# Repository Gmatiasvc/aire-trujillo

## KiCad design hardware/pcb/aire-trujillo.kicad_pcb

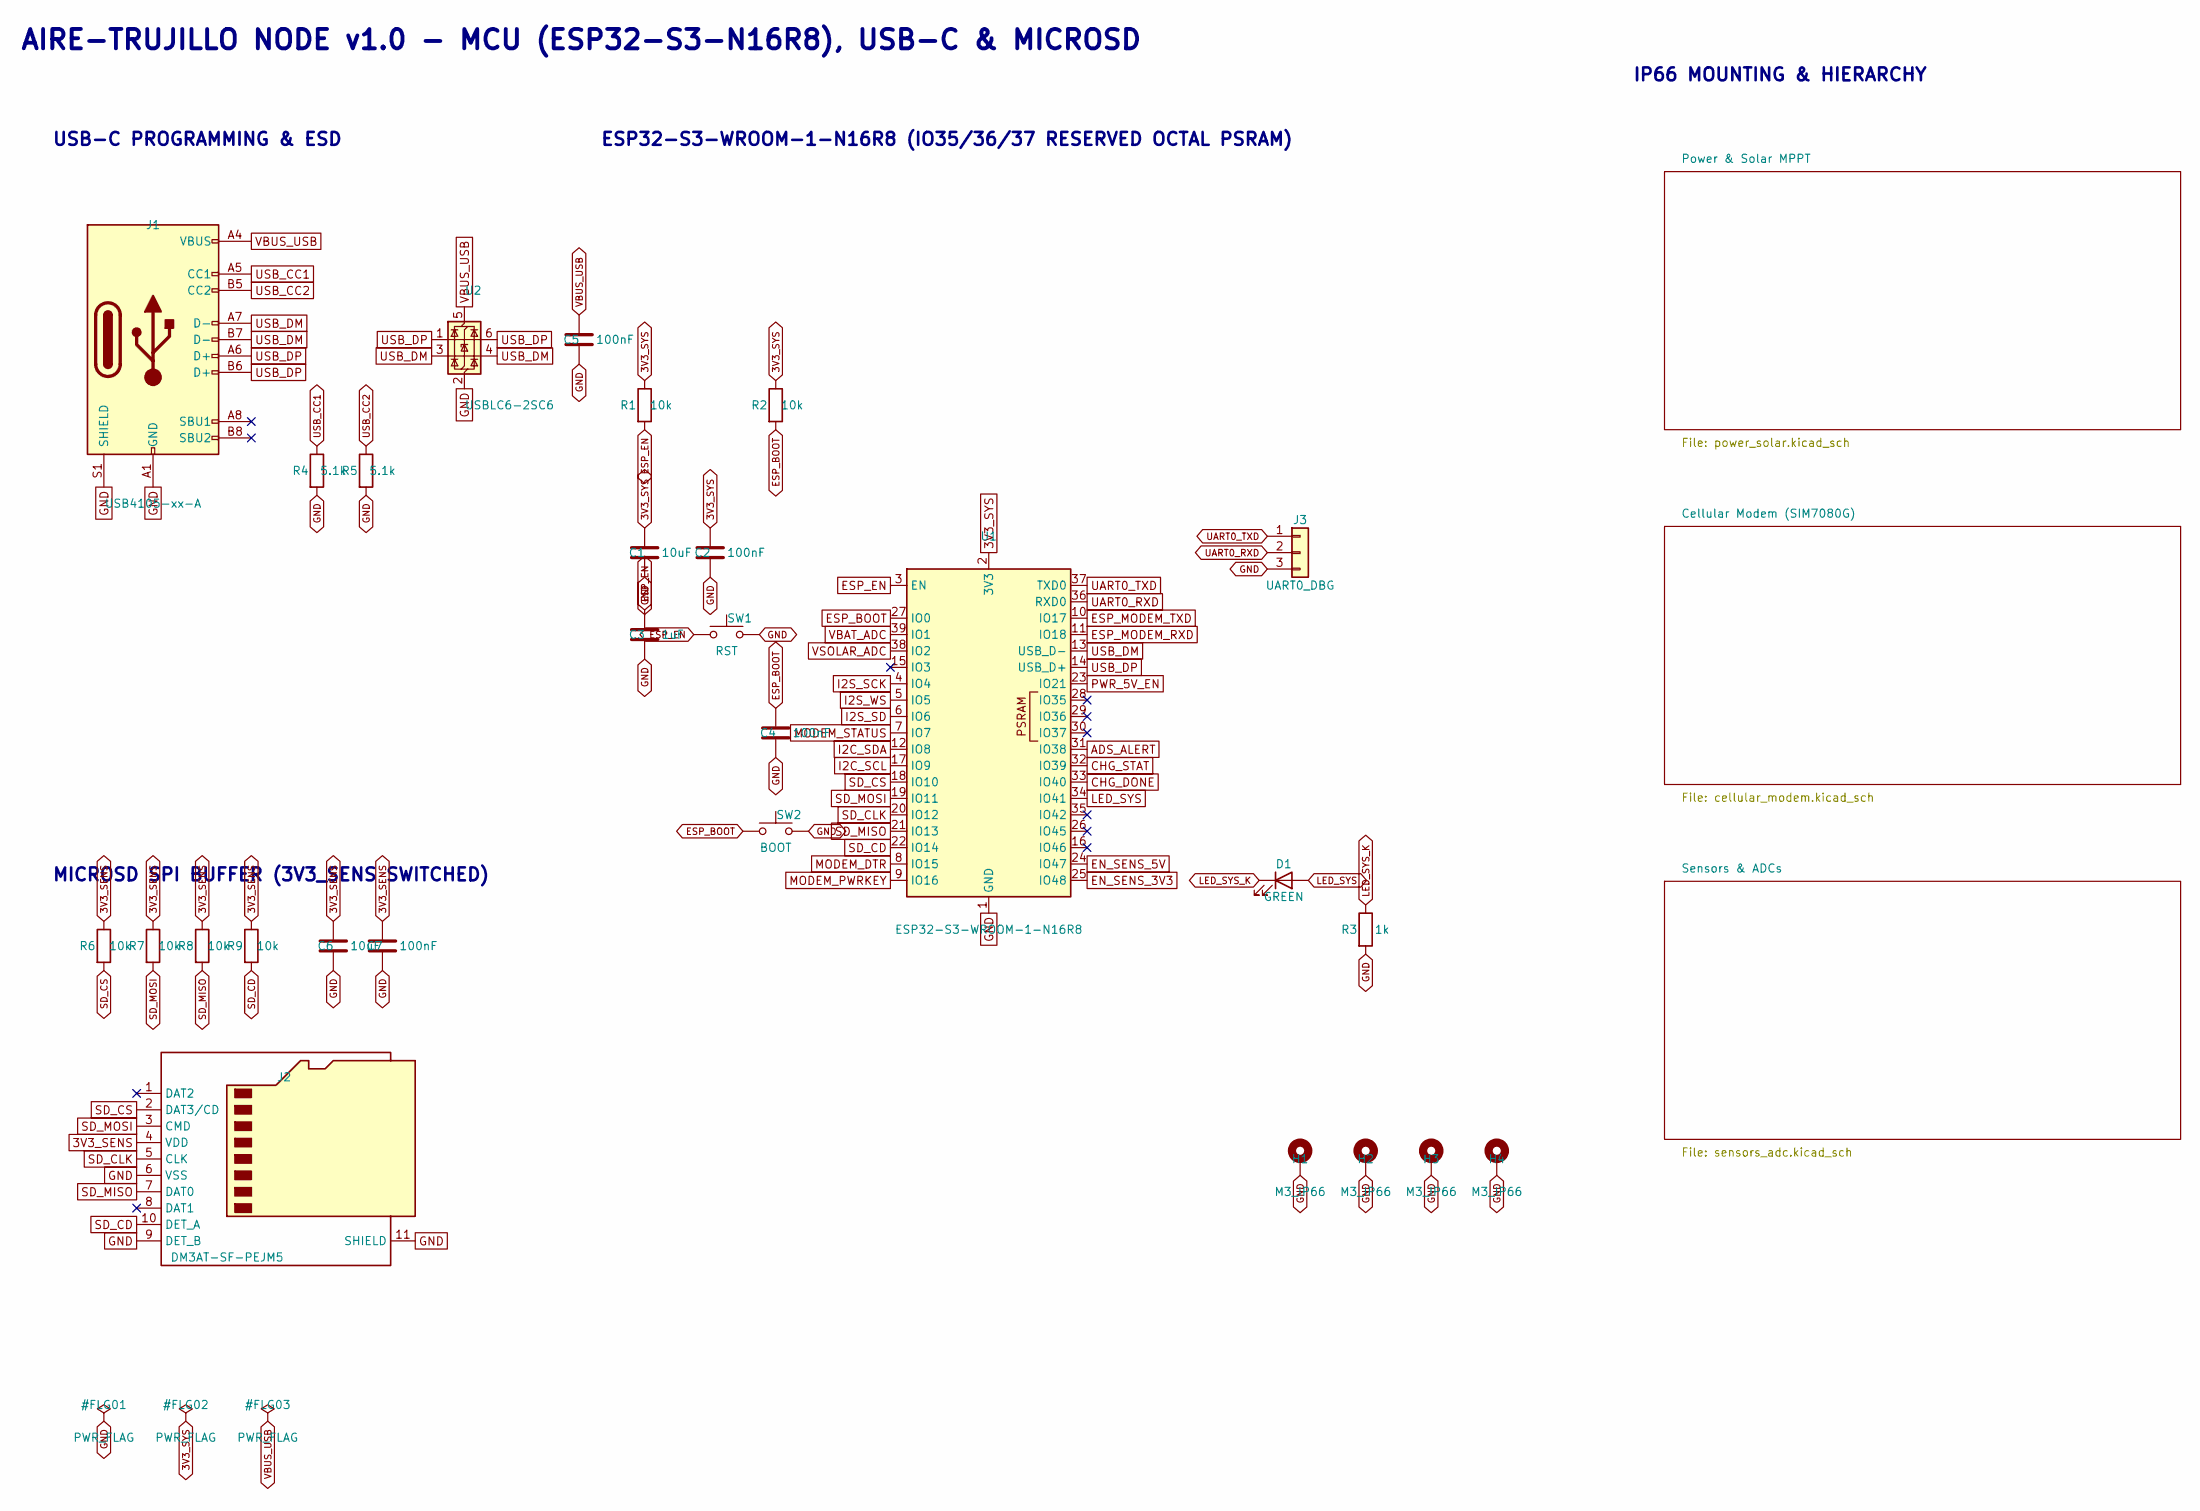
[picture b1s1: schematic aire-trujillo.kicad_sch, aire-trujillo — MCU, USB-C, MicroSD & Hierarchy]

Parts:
C1, C6: 10uF; C_0805_2012Metric
C2, C4, C5, C7: 100nF; C_0603_1608Metric
C3: 1uF; C_0603_1608Metric
D1: GREEN; LED_0603_1608Metric
H1, H2, H3, H4: M3_IP66; MountingHole_3.2mm_M3_ISO14580_Pad_TopBottom
J1: USB4105-xx-A; USB_C_Receptacle_GCT_USB4105-xx-A_16P_TopMnt_Horizontal
J2: DM3AT-SF-PEJM5; microSD_HC_Hirose_DM3AT-SF-PEJM5
J3: UART0_DBG; PinHeader_1x03_P2.54mm_Vertical
R1, R2, R6, R7, R8, R9: 10k; R_0603_1608Metric
R3: 1k; R_0603_1608Metric
R4, R5: 5.1k; R_0603_1608Metric
SW1: RST; SW_SPST_B3U-1000P
SW2: BOOT; SW_SPST_B3U-1000P
U1: ESP32-S3-WROOM-1-N16R8; ESP32-S3-WROOM-1
U2: USBLC6-2SC6; SOT-23-6

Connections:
3V3_SENS: C6.1, C7.1, J2.4 (VDD), R6.1, R7.1, R8.1, R9.1; also elsewhere on the board
3V3_SYS: C1.1, C2.1, R1.1, R2.1, U1.2 (3V3); also elsewhere on the board
ADS_ALERT: U1.31 (IO38); also elsewhere on the board
CHG_DONE: U1.33 (IO40); also elsewhere on the board
CHG_STAT: U1.32 (IO39); also elsewhere on the board
EN_SENS_3V3: U1.25 (IO48); also elsewhere on the board
EN_SENS_5V: U1.24 (IO47); also elsewhere on the board
ESP_BOOT: C4.1, R2.2, SW2.1, U1.27 (IO0)
ESP_EN: C3.1, R1.2, SW1.1, U1.3 (EN)
ESP_MODEM_RXD: U1.11 (IO18); also elsewhere on the board
ESP_MODEM_TXD: U1.10 (IO17); also elsewhere on the board
GND: C1.2, C2.2, C3.2, C4.2, C5.2, C6.2, C7.2, H1.1, H2.1, H3.1, H4.1, J1.A1 (GND), J1.A12 (GND), J1.B1 (GND), J1.B12 (GND), J1.S1 (SHIELD), J2.6 (VSS), J2.9 (DET_B), J2.11 (SHIELD), J3.3, R3.2, R4.2, R5.2, SW1.2, SW2.2, U1.1 (GND), U1.40 (GND), U1.41 (GND), U2.2 (GND); also elsewhere on the board
I2C_SCL: U1.17 (IO9); also elsewhere on the board
I2C_SDA: U1.12 (IO8); also elsewhere on the board
I2S_SCK: U1.4 (IO4); also elsewhere on the board
I2S_SD: U1.6 (IO6); also elsewhere on the board
I2S_WS: U1.5 (IO5); also elsewhere on the board
LED_SYS: D1.2 (A), U1.34 (IO41)
LED_SYS_K: D1.1 (K), R3.1
MODEM_DTR: U1.8 (IO15); also elsewhere on the board
MODEM_PWRKEY: U1.9 (IO16); also elsewhere on the board
MODEM_STATUS: U1.7 (IO7); also elsewhere on the board
PWR_5V_EN: U1.23 (IO21); also elsewhere on the board
SD_CD: J2.10 (DET_A), R9.2, U1.22 (IO14)
SD_CLK: J2.5 (CLK), U1.20 (IO12)
SD_CS: J2.2 (DAT3/CD), R6.2, U1.18 (IO10)
SD_MISO: J2.7 (DAT0), R8.2, U1.21 (IO13)
SD_MOSI: J2.3 (CMD), R7.2, U1.19 (IO11)
UART0_RXD: J3.2, U1.36 (RXD0)
UART0_TXD: J3.1, U1.37 (TXD0)
USB_CC1: J1.A5 (CC1), R4.1
USB_CC2: J1.B5 (CC2), R5.1
USB_DM: J1.A7 (D-), J1.B7 (D-), U1.13 (USB_D-), U2.3 (I/O2), U2.4 (I/O2)
USB_DP: J1.A6 (D+), J1.B6 (D+), U1.14 (USB_D+), U2.1 (I/O1), U2.6 (I/O1)
VBAT_ADC: U1.39 (IO1); also elsewhere on the board
VBUS_USB: C5.1, J1.A4 (VBUS), J1.A9 (VBUS), J1.B4 (VBUS), J1.B9 (VBUS), U2.5 (VBUS); also elsewhere on the board
VSOLAR_ADC: U1.38 (IO2); also elsewhere on the board

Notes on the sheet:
AIRE-TRUJILLO NODE v1.0 - MCU (ESP32-S3-N16R8), USB-C & MICROSD
USB-C PROGRAMMING & ESD
ESP32-S3-WROOM-1-N16R8 (IO35/36/37 RESERVED OCTAL PSRAM)
MICROSD SPI BUFFER (3V3_SENS SWITCHED)
IP66 MOUNTING & HIERARCHY

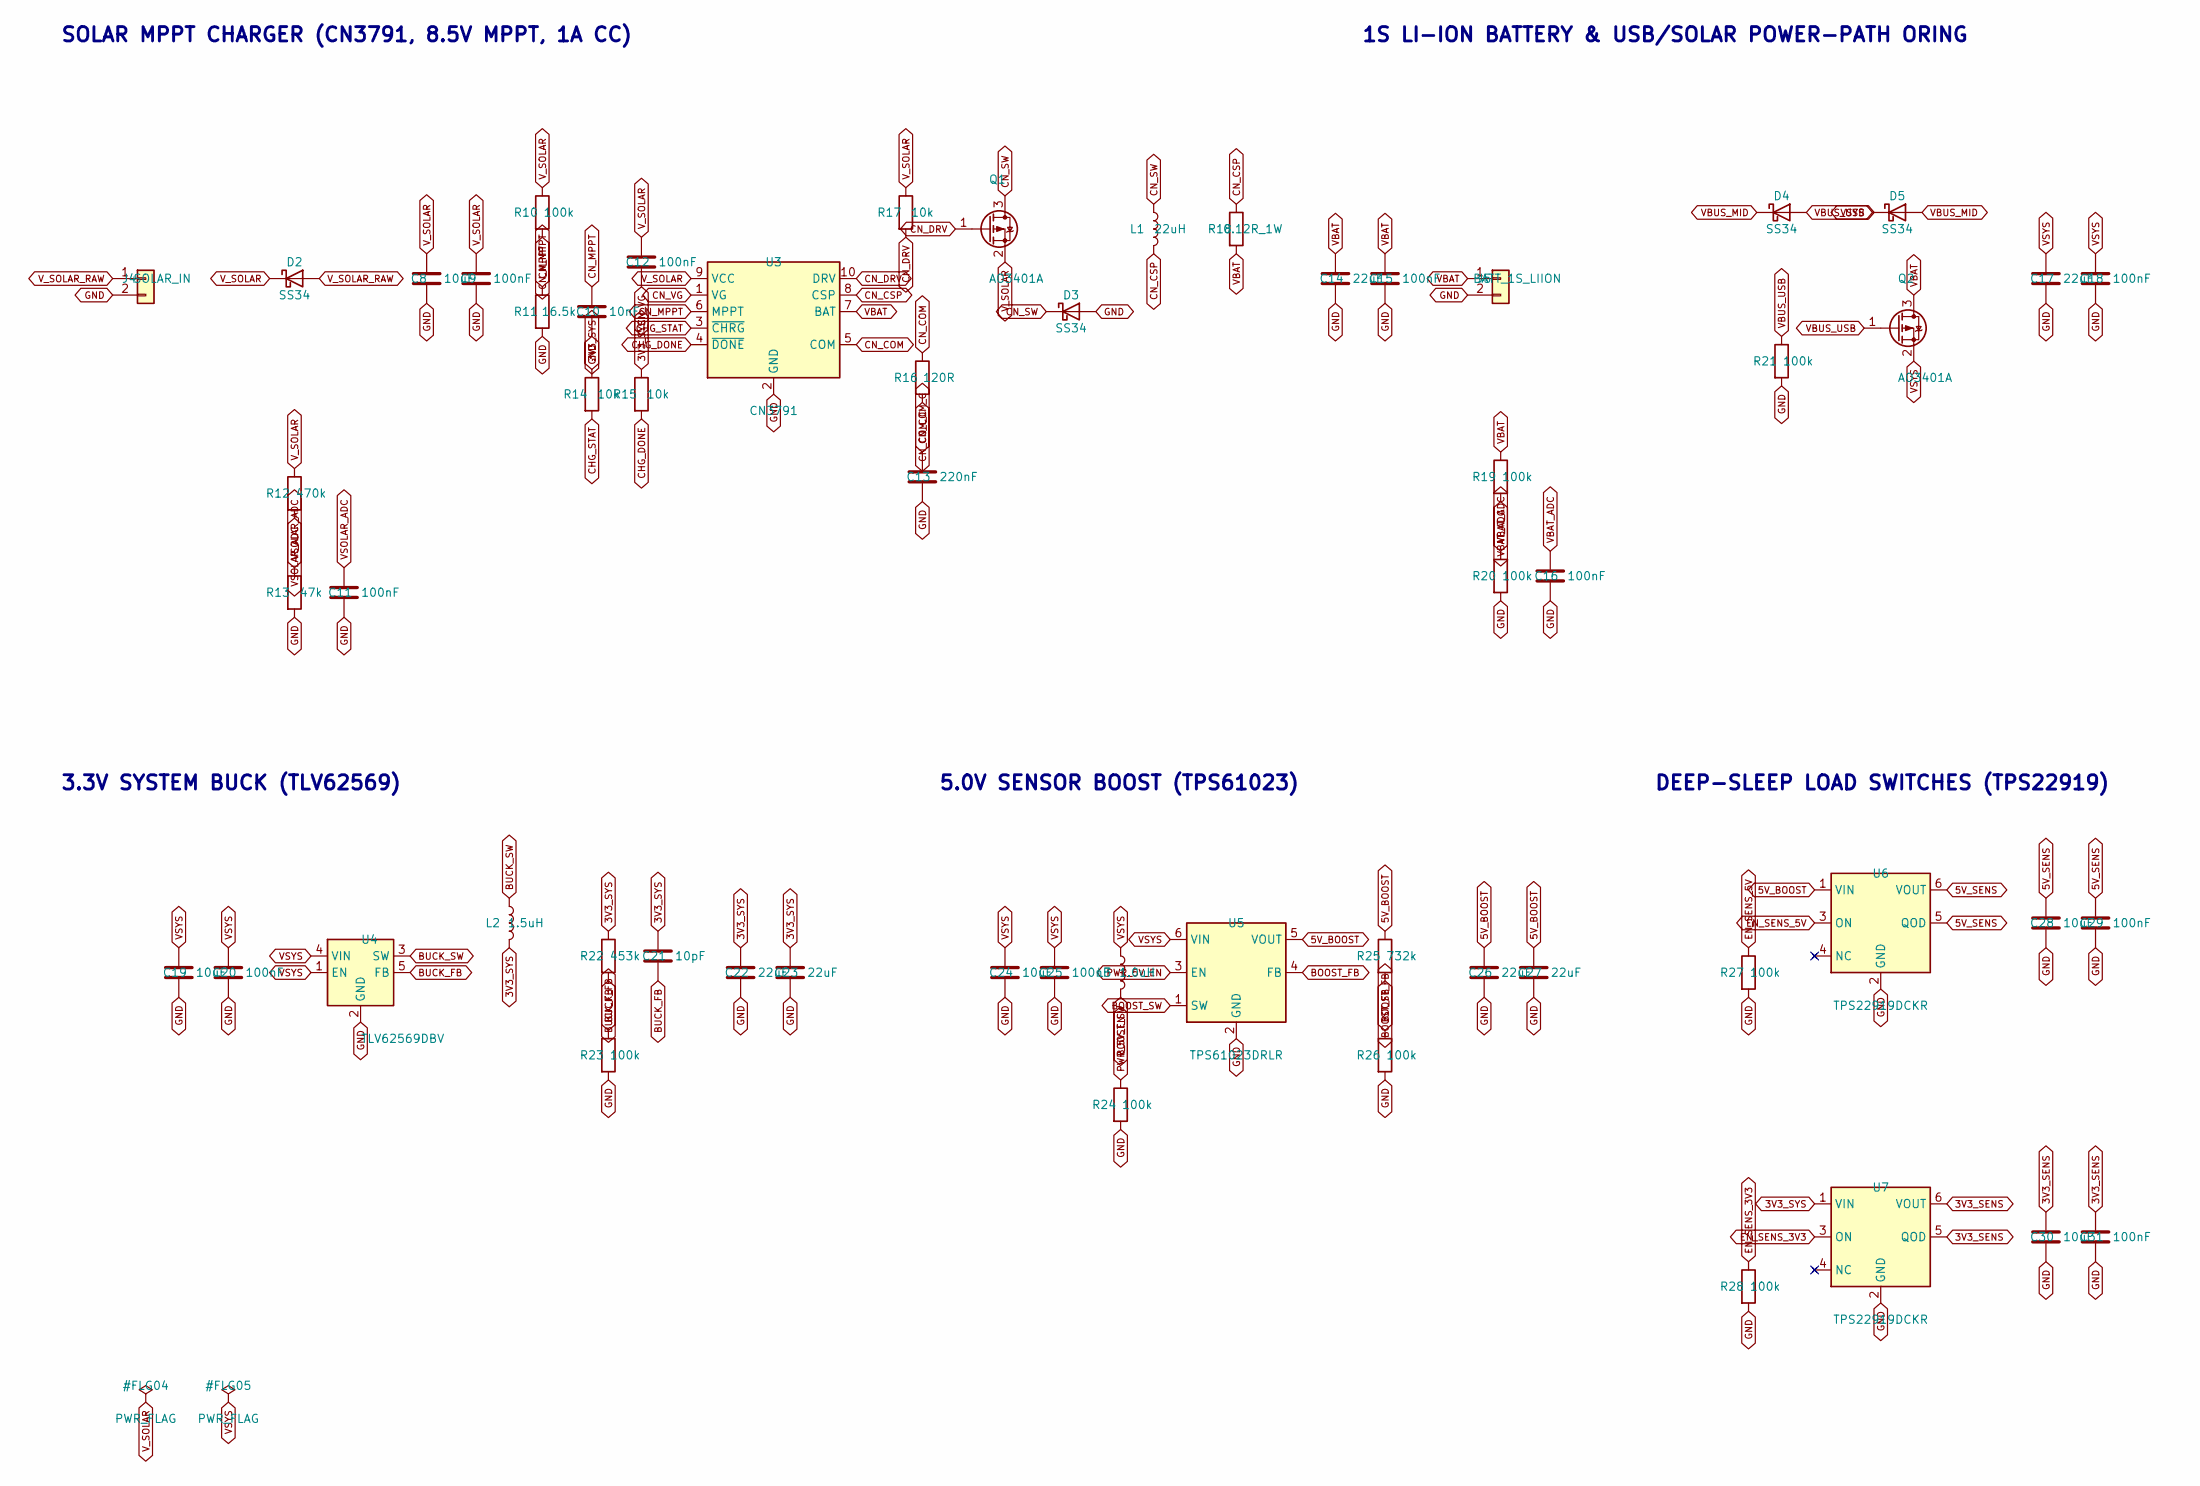
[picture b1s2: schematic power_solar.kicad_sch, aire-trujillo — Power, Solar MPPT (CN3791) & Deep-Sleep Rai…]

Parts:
C8, C19, C24, C28, C30: 10uF; C_0805_2012Metric
C9, C11, C12, C15, C16, C18, C20, C25, C29, C31: 100nF; C_0603_1608Metric
C10: 10nF; C_0603_1608Metric
C13: 220nF; C_0603_1608Metric
C14, C17, C22, C23, C26, C27: 22uF; C_0805_2012Metric
C21: 10pF; C_0603_1608Metric
D2, D3, D4, D5: SS34; D_SMA
J4: SOLAR_IN; JST_XH_B2B-XH-A_1x02_P2.50mm_Vertical
J5: BATT_1S_LIION; JST_XH_B2B-XH-A_1x02_P2.50mm_Vertical
L1: 22uH; L_Bourns_SRP5030T
L2: 1.5uH; L_Bourns-SRN4018
L3: 1.0uH; L_Bourns-SRN4018
Q1, Q2: AO3401A; SOT-23
R10, R19, R20, R21, R23, R24, R26, R27, R28: 100k; R_0603_1608Metric
R11: 16.5k; R_0603_1608Metric
R12: 470k; R_0603_1608Metric
R13: 47k; R_0603_1608Metric
R14, R15, R17: 10k; R_0603_1608Metric
R16: 120R; R_0603_1608Metric
R18: 0.12R_1W; R_1206_3216Metric
R22: 453k; R_0603_1608Metric
R25: 732k; R_0603_1608Metric
U3: CN3791; cn3791
U4: TLV62569DBV; SOT-23-5
U5: TPS61023DRLR; SOT-563
U6, U7: TPS22919DCKR; SOT-363_SC-70-6

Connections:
3V3_SENS: C30.1, C31.1, U7.5 (QOD), U7.6 (VOUT); also elsewhere on the board
3V3_SYS: C21.1, C22.1, C23.1, L2.2, R14.1, R15.1, R22.1, U7.1 (VIN); also elsewhere on the board
5V_BOOST: C26.1, C27.1, R25.1, U5.5 (VOUT), U6.1 (VIN)
5V_SENS: C28.1, C29.1, U6.5 (QOD), U6.6 (VOUT); also elsewhere on the board
BOOST_FB: R25.2, R26.1, U5.4 (FB)
BOOST_SW: L3.2, U5.1 (SW)
BUCK_FB: C21.2, R22.2, R23.1, U4.5 (FB)
BUCK_SW: L2.1, U4.3 (SW)
CHG_DONE: R15.2, U3.4 (~DONE); also elsewhere on the board
CHG_STAT: R14.2, U3.3 (~CHRG); also elsewhere on the board
CN_COM: R16.1, U3.5 (COM)
CN_COM_C: C13.1, R16.2
CN_CSP: L1.2, R18.1, U3.8 (CSP)
CN_DRV: Q1.1 (G), R17.2, U3.10 (DRV)
CN_MPPT: C10.1, R10.2, R11.1, U3.6 (MPPT)
CN_SW: D3.1 (K), L1.1, Q1.3 (D)
CN_VG: C12.2, U3.1 (VG)
EN_SENS_3V3: R28.1, U7.3 (ON); also elsewhere on the board
EN_SENS_5V: R27.1, U6.3 (ON); also elsewhere on the board
GND: C8.2, C9.2, C10.2, C11.2, C13.2, C14.2, C15.2, C16.2, C17.2, C18.2, C19.2, C20.2, C22.2, C23.2, C24.2, C25.2, C26.2, C27.2, C28.2, C29.2, C30.2, C31.2, D3.2 (A), J4.2, J5.2, R11.2, R13.2, R20.2, R21.2, R23.2, R24.2, R26.2, R27.2, R28.2, U3.2 (GND), U4.2 (GND), U5.2 (GND), U6.2 (GND), U7.2 (GND); also elsewhere on the board
PWR_5V_EN: R24.1, U5.3 (EN); also elsewhere on the board
VBAT: C14.1, C15.1, J5.1, Q2.3 (D), R18.2, R19.1, U3.7 (BAT)
VBAT_ADC: C16.1, R19.2, R20.1; also elsewhere on the board
VBUS_MID: D4.1 (K), D5.2 (A)
VBUS_USB: D4.2 (A), Q2.1 (G), R21.1; also elsewhere on the board
VSOLAR_ADC: C11.1, R12.2, R13.1; also elsewhere on the board
VSYS: C17.1, C18.1, C19.1, C20.1, C24.1, C25.1, D5.1 (K), L3.1, Q2.2 (S), U4.1 (EN), U4.4 (VIN), U5.6 (VIN); also elsewhere on the board
V_SOLAR: C8.1, C9.1, C12.1, D2.1 (K), Q1.2 (S), R10.1, R12.1, R17.1, U3.9 (VCC)
V_SOLAR_RAW: D2.2 (A), J4.1

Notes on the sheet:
SOLAR MPPT CHARGER (CN3791, 8.5V MPPT, 1A CC)
1S LI-ION BATTERY & USB/SOLAR POWER-PATH ORING
3.3V SYSTEM BUCK (TLV62569)
5.0V SENSOR BOOST (TPS61023)
DEEP-SLEEP LOAD SWITCHES (TPS22919)

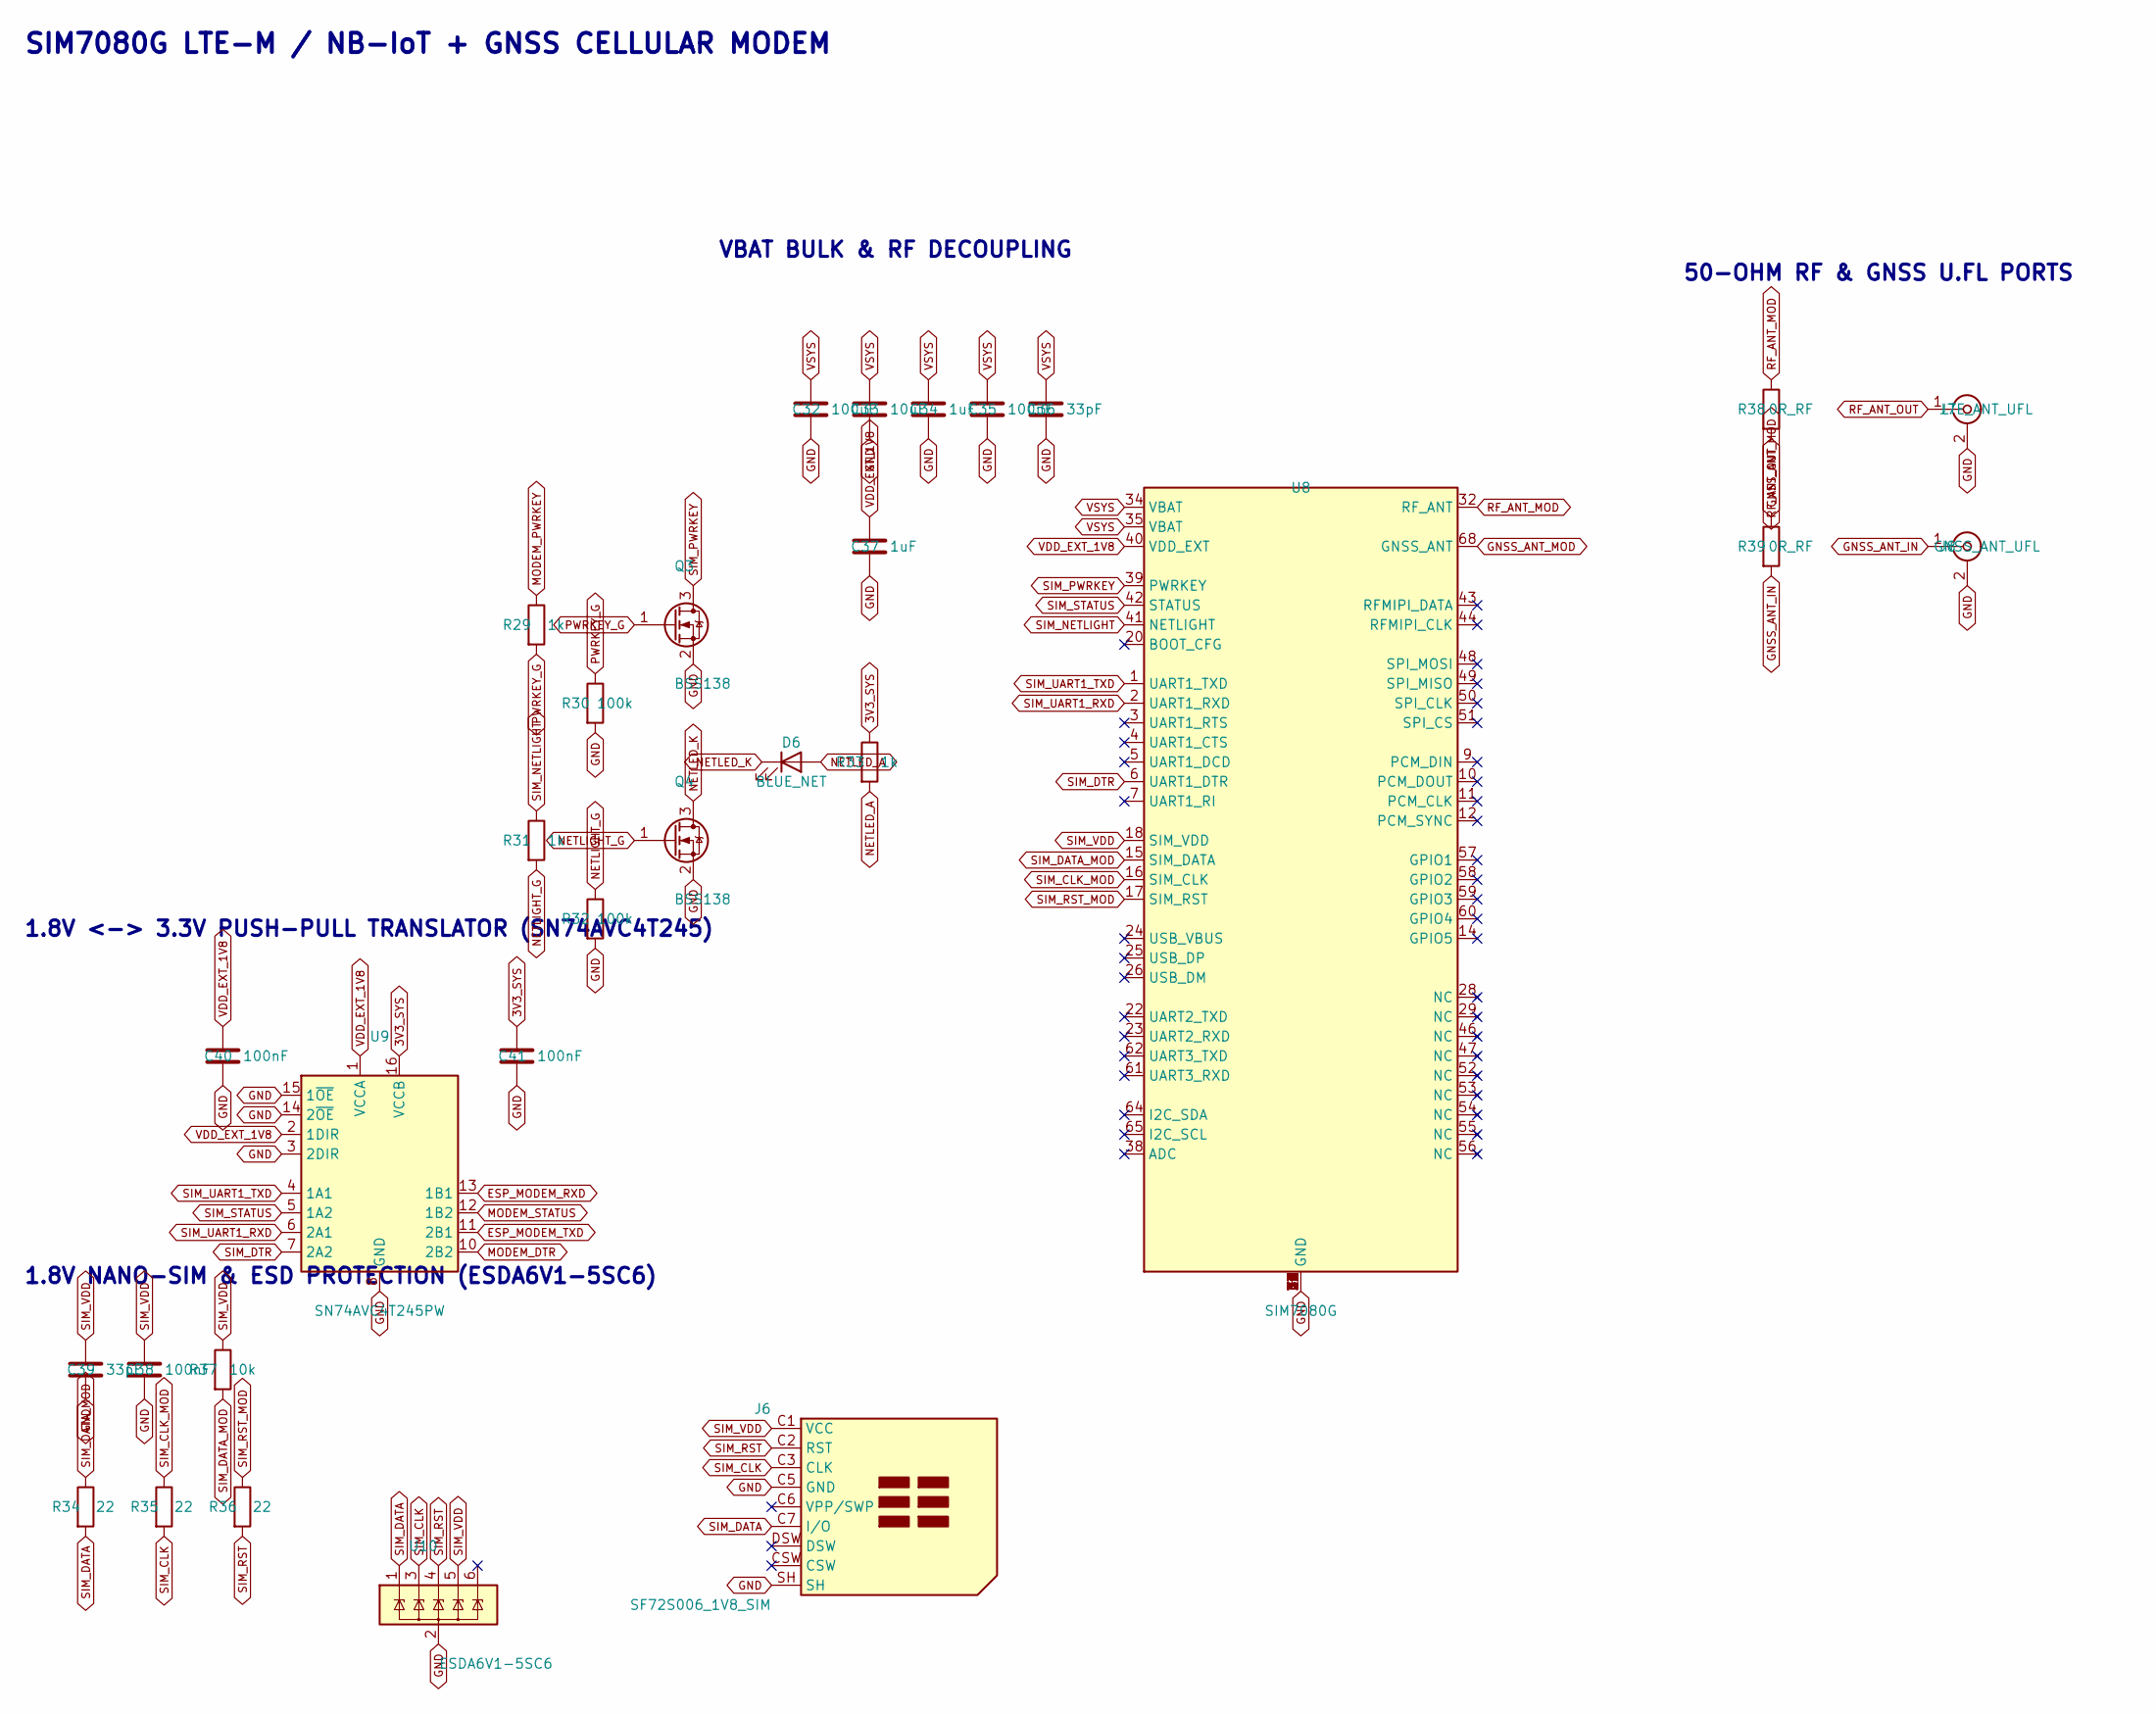
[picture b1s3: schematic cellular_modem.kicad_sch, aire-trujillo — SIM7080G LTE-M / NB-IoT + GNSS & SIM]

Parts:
C32: 100uF; C_1206_3216Metric
C33: 10uF; C_0805_2012Metric
C34, C37: 1uF; C_0603_1608Metric
C35, C38, C40, C41: 100nF; C_0603_1608Metric
C36, C39: 33pF; C_0603_1608Metric
D6: BLUE_NET; LED_0603_1608Metric
J6: SF72S006_1V8_SIM; JAE_SIM_Card_SF72S006
J7: LTE_ANT_UFL; U.FL_Hirose_U.FL-R-SMT-1_Vertical
J8: GNSS_ANT_UFL; U.FL_Hirose_U.FL-R-SMT-1_Vertical
Q3, Q4: BSS138; SOT-23
R29, R31, R33: 1k; R_0603_1608Metric
R30, R32: 100k; R_0603_1608Metric
R34, R35, R36: 22; R_0603_1608Metric
R37: 10k; R_0603_1608Metric
R38, R39: 0R_RF; R_0603_1608Metric
U8: SIM7080G; SIMCom_SIM7080G
U9: SN74AVC4T245PW; TSSOP-16_4.4x5mm_P0.65mm
U10: ESDA6V1-5SC6; SOT-23-6

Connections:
3V3_SYS: C41.1, R33.1, U9.16 (VCCB); also elsewhere on the board
ESP_MODEM_RXD: U9.13 (1B1); also elsewhere on the board
ESP_MODEM_TXD: U9.11 (2B1); also elsewhere on the board
GND: C32.2, C33.2, C34.2, C35.2, C36.2, C37.2, C38.2, C39.2, C40.2, C41.2, J6.C5 (GND), J6.SH, J7.2 (Ext), J8.2 (Ext), Q3.2 (S), Q4.2 (S), R30.2, R32.2, U8.8 (GND), U8.13 (GND), U8.19 (GND), U8.21 (GND), U8.27 (GND), U8.30 (GND), U8.31 (GND), U8.33 (GND), U8.36 (GND), U8.37 (GND), U8.45 (GND), U8.63 (GND), U8.66 (GND), U8.67 (GND), U8.69 (GND), U8.70 (GND), U8.71 (GND), U8.72 (GND), U8.73 (GND), U8.74 (GND), U8.75 (GND), U8.76 (GND), U8.77 (GND), U9.3 (2DIR), U9.8 (GND), U9.9 (GND), U9.14 (2~OE), U9.15 (1~OE), U10.2 (GND); also elsewhere on the board
GNSS_ANT_IN: J8.1 (In), R39.2
GNSS_ANT_MOD: R39.1, U8.68 (GNSS_ANT)
MODEM_DTR: U9.10 (2B2); also elsewhere on the board
MODEM_PWRKEY: R29.1; also elsewhere on the board
MODEM_STATUS: U9.12 (1B2); also elsewhere on the board
NETLED_A: D6.2 (A), R33.2
NETLED_K: D6.1 (K), Q4.3 (D)
NETLIGHT_G: Q4.1 (G), R31.2, R32.1
PWRKEY_G: Q3.1 (G), R29.2, R30.1
RF_ANT_MOD: R38.1, U8.32 (RF_ANT)
RF_ANT_OUT: J7.1 (In), R38.2
SIM_CLK: J6.C3 (CLK), R35.2, U10.3 (IO2)
SIM_CLK_MOD: R35.1, U8.16 (SIM_CLK)
SIM_DATA: J6.C7 (I/O), R34.2, U10.1 (IO1)
SIM_DATA_MOD: R34.1, R37.2, U8.15 (SIM_DATA)
SIM_DTR: U8.6 (UART1_DTR), U9.7 (2A2)
SIM_NETLIGHT: R31.1, U8.41 (NETLIGHT)
SIM_PWRKEY: Q3.3 (D), U8.39 (PWRKEY)
SIM_RST: J6.C2 (RST), R36.2, U10.4 (IO3)
SIM_RST_MOD: R36.1, U8.17 (SIM_RST)
SIM_STATUS: U8.42 (STATUS), U9.5 (1A2)
SIM_UART1_RXD: U8.2 (UART1_RXD), U9.6 (2A1)
SIM_UART1_TXD: U8.1 (UART1_TXD), U9.4 (1A1)
SIM_VDD: C38.1, C39.1, J6.C1 (VCC), R37.1, U8.18 (SIM_VDD), U10.5 (IO4)
VDD_EXT_1V8: C37.1, C40.1, U8.40 (VDD_EXT), U9.1 (VCCA), U9.2 (1DIR)
VSYS: C32.1, C33.1, C34.1, C35.1, C36.1, U8.34 (VBAT), U8.35 (VBAT); also elsewhere on the board

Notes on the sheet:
SIM7080G LTE-M / NB-IoT + GNSS CELLULAR MODEM
VBAT BULK & RF DECOUPLING
1.8V <-> 3.3V PUSH-PULL TRANSLATOR (SN74AVC4T245)
1.8V NANO-SIM & ESD PROTECTION (ESDA6V1-5SC6)
50-OHM RF & GNSS U.FL PORTS

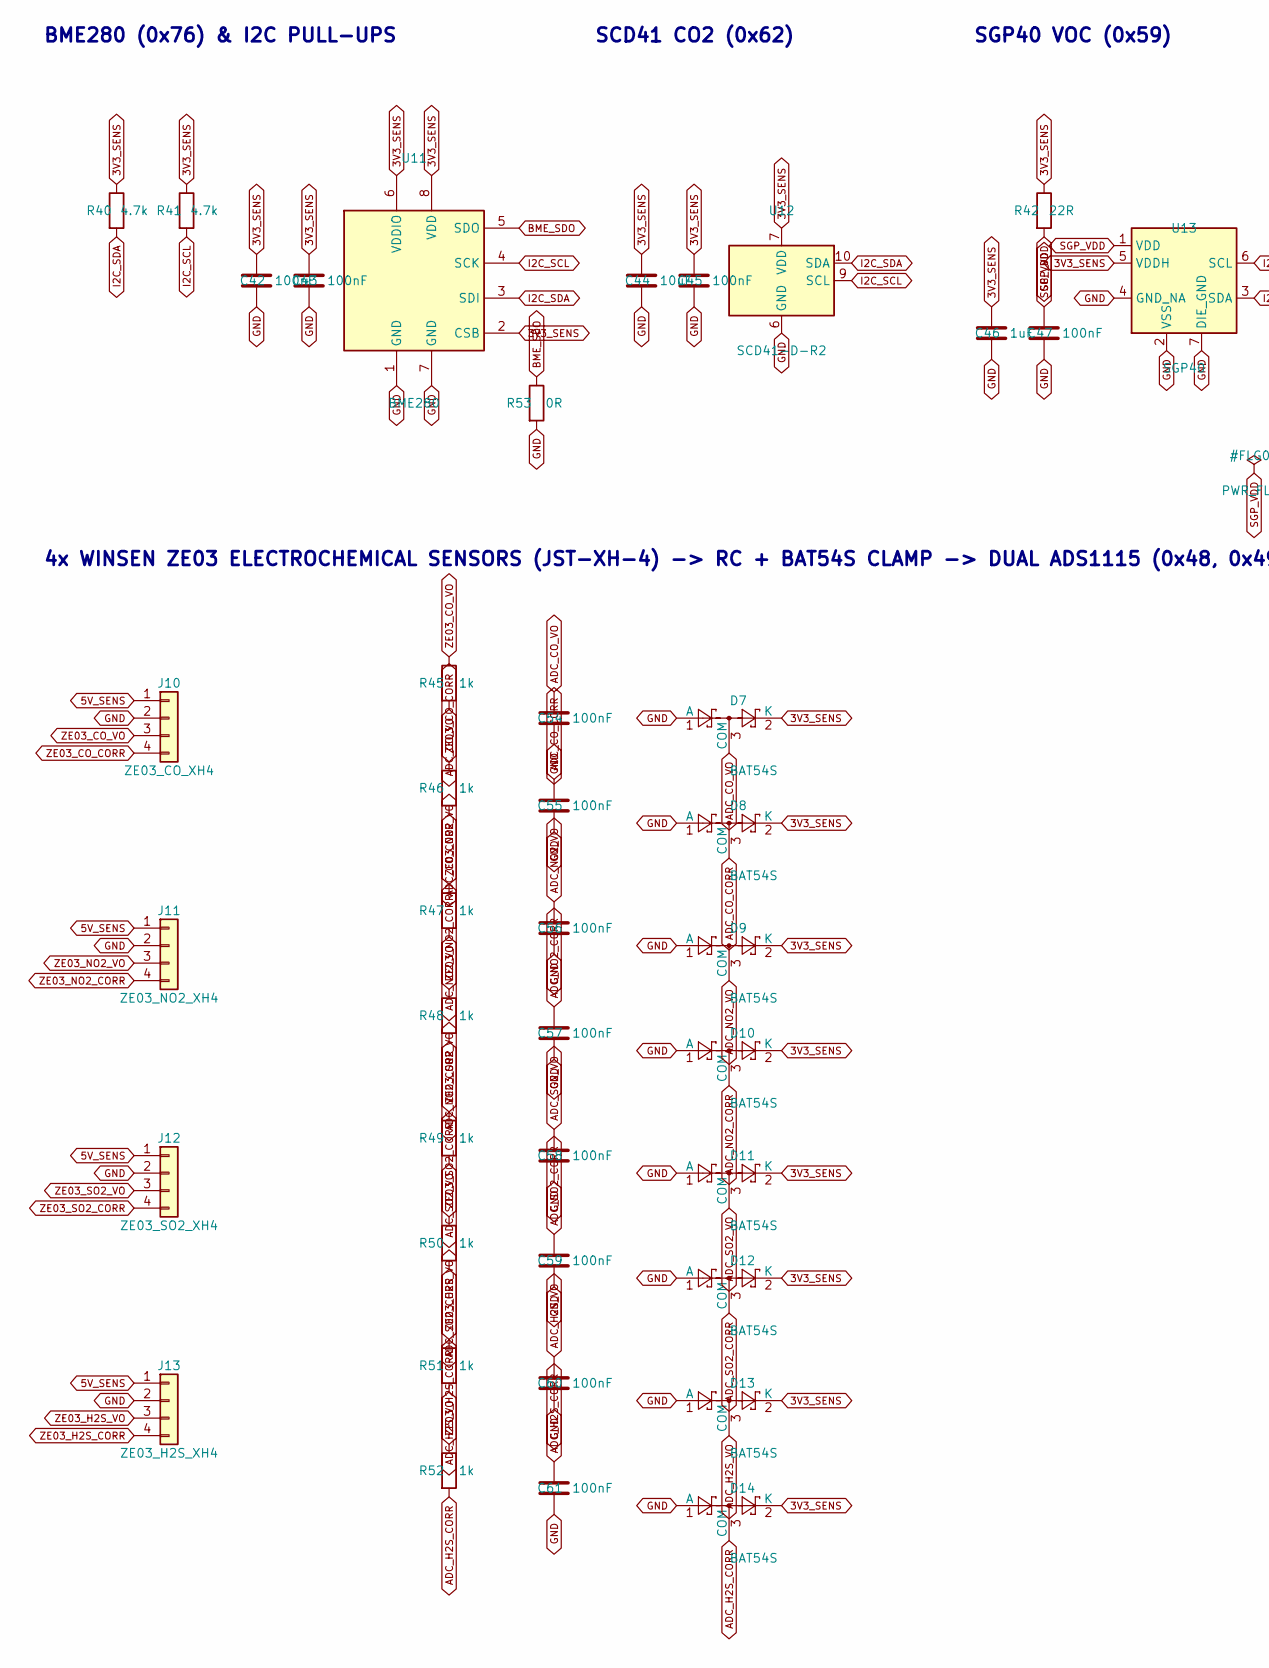
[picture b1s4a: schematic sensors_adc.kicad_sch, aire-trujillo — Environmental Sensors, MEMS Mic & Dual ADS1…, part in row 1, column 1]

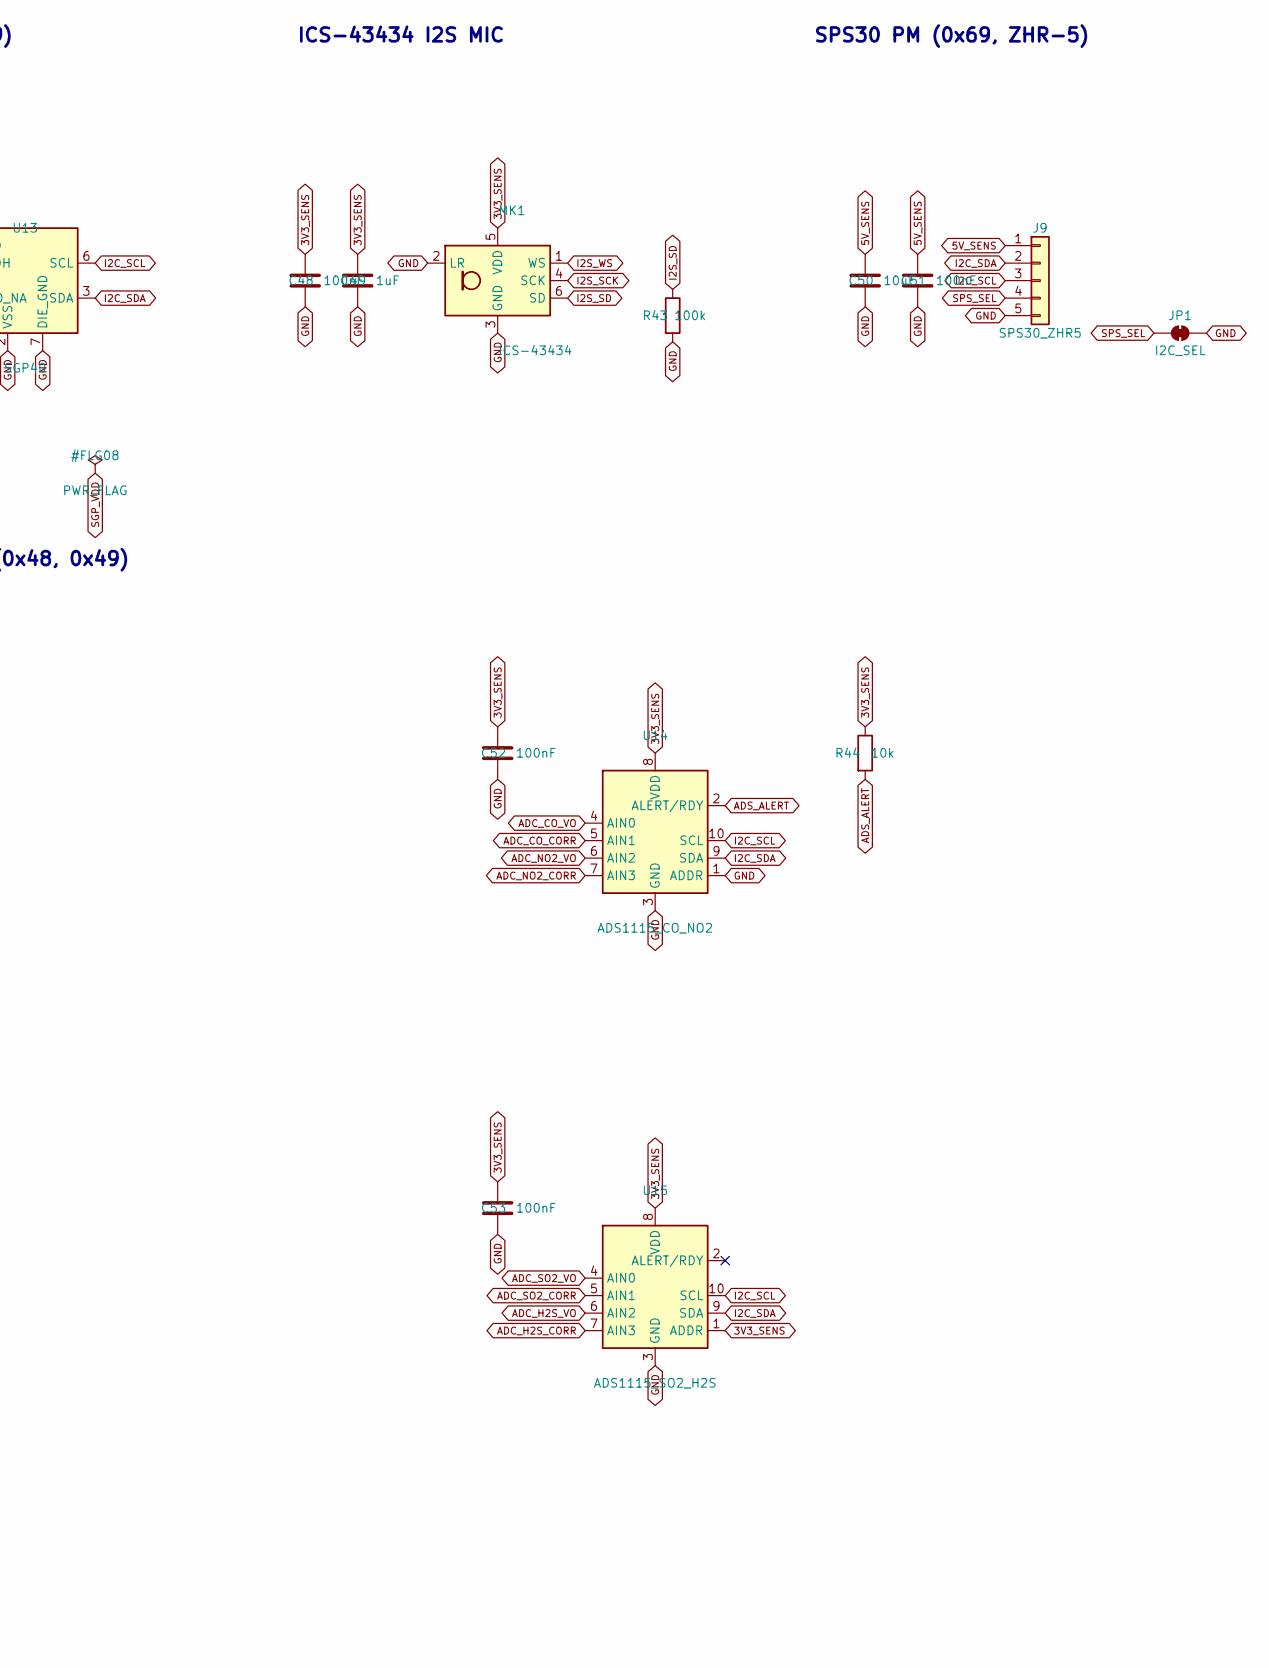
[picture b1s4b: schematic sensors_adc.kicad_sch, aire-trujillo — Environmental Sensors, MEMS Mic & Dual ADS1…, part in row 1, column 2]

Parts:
C42, C43, C45, C47, C48, C51, C52, C53, C54, C55, C56, C57, C58, C59, C60, C61: 100nF; C_0603_1608Metric
C44, C50: 10uF; C_0805_2012Metric
C46, C49: 1uF; C_0603_1608Metric
D7, D8, D9, D10, D11, D12, D13, D14: BAT54S; SOT-323_SC-70
J9: SPS30_ZHR5; JST_ZH_B5B-ZR-SM4-TF_1x05-1MP_P1.50mm_Vertical
J10: ZE03_CO_XH4; JST_XH_B4B-XH-A_1x04_P2.50mm_Vertical
J11: ZE03_NO2_XH4; JST_XH_B4B-XH-A_1x04_P2.50mm_Vertical
J12: ZE03_SO2_XH4; JST_XH_B4B-XH-A_1x04_P2.50mm_Vertical
J13: ZE03_H2S_XH4; JST_XH_B4B-XH-A_1x04_P2.50mm_Vertical
JP1: I2C_SEL; SolderJumper-2_P1.3mm_Bridged_RoundedPad1.0x1.5mm
MK1: ICS-43434; InvenSense_ICS-43434-6_3.5x2.65mm
R40, R41: 4.7k; R_0603_1608Metric
R42: 22R; R_0603_1608Metric
R43: 100k; R_0603_1608Metric
R44: 10k; R_0603_1608Metric
R45, R46, R47, R48, R49, R50, R51, R52: 1k; R_0603_1608Metric
R53: 0R; R_0603_1608Metric
U11: BME280; Bosch_LGA-8_2.5x2.5mm_P0.65mm_ClockwisePinNumbering
U12: SCD41-D-R2; Sensirion_SCD4x-1EP_10.1x10.1mm_P1.25mm_EP4.8x4.8mm
U13: SGP40; sgp40
U14: ADS1115_CO_NO2; TSSOP-10_3x3mm_P0.5mm
U15: ADS1115_SO2_H2S; TSSOP-10_3x3mm_P0.5mm

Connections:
3V3_SENS: C42.1, C43.1, C44.1, C45.1, C46.1, C48.1, C49.1, C52.1, C53.1, D7.2 (K), D8.2 (K), D9.2 (K), D10.2 (K), D11.2 (K), D12.2 (K), D13.2 (K), D14.2 (K), MK1.5 (VDD), R40.1, R41.1, R42.1, R44.1, U11.2 (CSB), U11.6 (VDDIO), U11.8 (VDD), U12.7 (VDD), U12.19 (VDD), U13.5 (VDDH), U14.8 (VDD), U15.1 (ADDR), U15.8 (VDD); also elsewhere on the board
5V_SENS: C50.1, C51.1, J9.1, J10.1, J11.1, J12.1, J13.1; also elsewhere on the board
ADC_CO_CORR: C55.1, D8.3 (COM), R46.2, U14.5 (AIN1)
ADC_CO_VO: C54.1, D7.3 (COM), R45.2, U14.4 (AIN0)
ADC_H2S_CORR: C61.1, D14.3 (COM), R52.2, U15.7 (AIN3)
ADC_H2S_VO: C60.1, D13.3 (COM), R51.2, U15.6 (AIN2)
ADC_NO2_CORR: C57.1, D10.3 (COM), R48.2, U14.7 (AIN3)
ADC_NO2_VO: C56.1, D9.3 (COM), R47.2, U14.6 (AIN2)
ADC_SO2_CORR: C59.1, D12.3 (COM), R50.2, U15.5 (AIN1)
ADC_SO2_VO: C58.1, D11.3 (COM), R49.2, U15.4 (AIN0)
ADS_ALERT: R44.2, U14.2 (ALERT/RDY); also elsewhere on the board
BME_SDO: R53.1, U11.5 (SDO)
GND: C42.2, C43.2, C44.2, C45.2, C46.2, C47.2, C48.2, C49.2, C50.2, C51.2, C52.2, C53.2, C54.2, C55.2, C56.2, C57.2, C58.2, C59.2, C60.2, C61.2, D7.1 (A), D8.1 (A), D9.1 (A), D10.1 (A), D11.1 (A), D12.1 (A), D13.1 (A), D14.1 (A), J9.5, J10.2, J11.2, J12.2, J13.2, JP1.2 (B), MK1.2 (LR), MK1.3 (GND), R43.2, R53.2, U11.1 (GND), U11.7 (GND), U12.6 (GND), U12.20 (GND), U12.21 (GND), U13.2 (VSS), U13.4 (GND_NA), U13.7 (DIE_GND), U14.1 (ADDR), U14.3 (GND), U15.3 (GND); also elsewhere on the board
I2C_SCL: J9.3, R41.2, U11.4 (SCK), U12.9 (SCL), U13.6 (SCL), U14.10 (SCL), U15.10 (SCL); also elsewhere on the board
I2C_SDA: J9.2, R40.2, U11.3 (SDI), U12.10 (SDA), U13.3 (SDA), U14.9 (SDA), U15.9 (SDA); also elsewhere on the board
I2S_SCK: MK1.4 (SCK); also elsewhere on the board
I2S_SD: MK1.6 (SD), R43.1; also elsewhere on the board
I2S_WS: MK1.1 (WS); also elsewhere on the board
SGP_VDD: C47.1, R42.2, U13.1 (VDD)
SPS_SEL: J9.4, JP1.1 (A)
ZE03_CO_CORR: J10.4, R46.1
ZE03_CO_VO: J10.3, R45.1
ZE03_H2S_CORR: J13.4, R52.1
ZE03_H2S_VO: J13.3, R51.1
ZE03_NO2_CORR: J11.4, R48.1
ZE03_NO2_VO: J11.3, R47.1
ZE03_SO2_CORR: J12.4, R50.1
ZE03_SO2_VO: J12.3, R49.1

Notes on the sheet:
BME280 (0x76) & I2C PULL-UPS
SCD41 CO2 (0x62)
SGP40 VOC (0x59)
ICS-43434 I2S MIC
SPS30 PM (0x69, ZHR-5)
4x WINSEN ZE03 ELECTROCHEMICAL SENSORS (JST-XH-4) -> RC + BAT54S CLAMP -> DUAL ADS1115 (0x48, 0x49)
